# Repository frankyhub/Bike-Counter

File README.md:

<div align="center">

|[:skull:ISSUE](https://github.com/frankyhub/Bike-Counter/issues?q=is%3Aissue)|[:speech_balloon: Forum /Discussion](https://github.com/frankyhub/Bike-Counter/discussions)|[:grey_question:WiKi](https://github.com/frankyhub/Bike-Counter/wiki)||
|--|--|--|--|
| | | | |
||<a href="https://github.com/frankyhub/Bike-Counter/issues">|<a href="https://github.com/frankyhub/Bike-Counter/discussions">|<a href="https://github.com/frankyhub/Bike-Counter/releases">|
|| <a href="https://github.com/frankyhub/Bike-Counter/pulse" alt="Activity">| <a href="https://github.com/frankyhub/Bike-Counter/graphs/traffic">  |<a href="https://github.com/frankyhub?tab=stars"> |
</div>

# Bike-Counter

## Story
Der Bike-Counter zählt Bikes auf einer Nebenstraße in zwei unterschiedlichen Richtungen und sendet die Zählerstände an eine SQL-Datenbank. Es sollen nur Bikes gezählt werden und keine Fußgänger oder andere Fahrzeuge. Mit einem Dashboard werden die Zählerstände der Bikes angezeigt. Eine Auswertung zeigt die Durchfahrt der Bikes innerhalb der letzten 24 Stunden. Für die Erfassung der Bikes werden 2 Lichtschranken verwendet.

Vorteile des Bike-Counters: 
+ Verwendung von handelsüblichen Sensoren (Drucksensor, Lichtschranke ...)
+ Richtungserkennung der Fahrräder
+ Zählerstände auf einem Dashboard visualisiert
+ Auswertung der Bewegungen der letzten 24h
+ Nutzung der kostenlosen SQL-Datenbank des Providers (Strato)

## Hardware
+ 1 x ESP32
+ 2 x Lichtschranken PEM2D
+ 1 x Platine (Richtungserkennung)

## Software
+ Die Zählimpulse der Lichtschranken werden von der "Richtungserkennung-Platine" aufbereitet.
+ Der ESP32 übermittelt die Zählerstände an das PHP-Programm "post-data.php".
+ Die Zählerstände werden in einer SQL-Datenbank gespeichert und mit dem Dashboard "hoki-counter.php angezeigt.
+ Eine 24h-Auswertung kann mit dem Programm "auswertung.php" erfolgen.

---

<div style="position:absolute; left:2cm; ">   
<ol class="breadcrumb" style="border-top: 2px solid black;border-bottom:2px solid black; height: 45px; width: 900px;"> <p align="center"><a href="#oben">nach oben</a></p></ol>
</div>  

---

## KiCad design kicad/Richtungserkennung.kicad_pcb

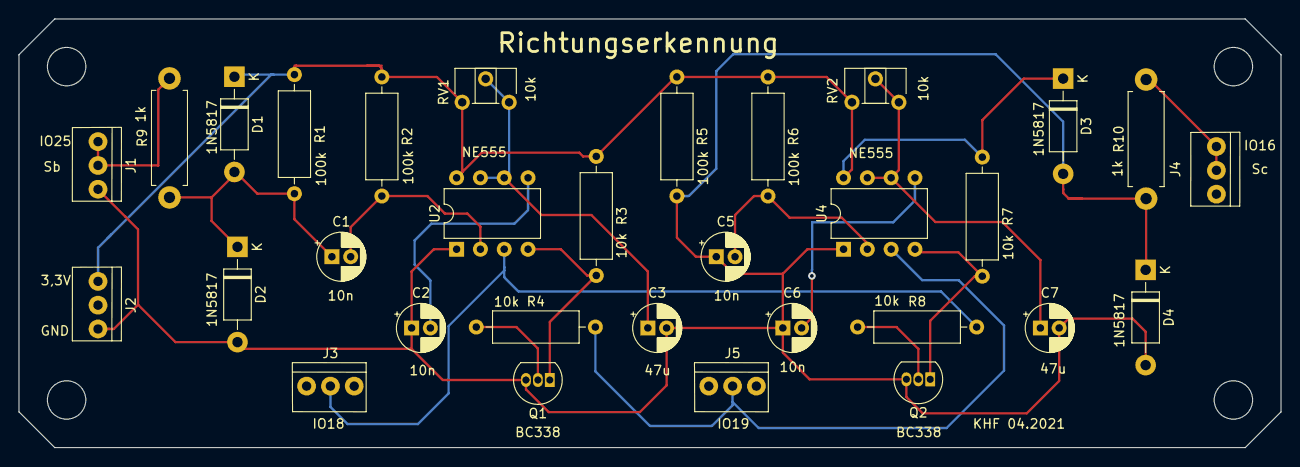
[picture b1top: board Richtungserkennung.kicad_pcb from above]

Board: 2 copper layers, 134.6 x 45.7 mm, 31 parts (0 on the bottom side), 17 nets.

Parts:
C1, C2, C5, C6: 10nF; CP_Radial_D5.0mm_P2.00mm
C3, C7: CP; CP_Radial_D5.0mm_P2.00mm
D1, D2, D3, D4: 1N5817; D_DO-41_SOD81_P10.16mm_Horizontal
J1, J2, J3, J4, J5: PL-Stecker_3pol_ohne_Beschriftung; PL-Stecker3pol
Q1, Q2: BC338; TO-92_Inline
R1, R2, R5, R6: 100k; R_Axial_DIN0309_L9.0mm_D3.2mm_P12.70mm_Horizontal
R3, R7: 10k; R_Axial_DIN0309_L9.0mm_D3.2mm_P12.70mm_Horizontal
R4, R8: R; R_Axial_DIN0309_L9.0mm_D3.2mm_P12.70mm_Horizontal
R9, R10: 1k; R_Axial_DIN0411_L9.9mm_D3.6mm_P12.70mm_Horizontal
RV1: 10k; Potentiometer_Piher_PT-6-H_Horizontal
RV2: 100k; Potentiometer_Piher_PT-6-H_Horizontal
U2, U4: NE555D; DIP-8_W7.62mm

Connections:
unnamed: C1.1, D1.2, D2.1, R1.2, R9.1
unnamed: C1.2, R2.2, U2.2
unnamed: C2.1, C3.2, C5.1, C6.1, C7.2, D2.2, D3.2, D4.1, D4.2, J1.3, J2.3, Q1.3, Q2.3, R5.2, R10.1, U2.1, U4.1
unnamed: C2.2, U2.5
unnamed: C3.1, RV1.2, RV1.3, U2.6, U2.7
unnamed: C5.2, R6.2, U4.2
unnamed: C6.2, U4.5
unnamed: C7.1, RV2.2, RV2.3, U4.6, U4.7
unnamed: D1.1, D3.1, J2.1, R1.1, R2.1, R3.1, R5.1, R6.1, R7.1, RV1.1, RV2.1, U2.8, U4.8
unnamed: J1.1, J1.2, R9.2
unnamed: J3.2, R8.2, U2.3
unnamed: J4.1, J4.2, R10.2
unnamed: J5.2, R4.2, U4.3
unnamed: Q1.1, R3.2, U2.4
unnamed: Q1.2, R4.1
unnamed: Q2.1, R7.2, U4.4
unnamed: Q2.2, R8.1

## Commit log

2024-08-16 V 28.06.2021
2024-10-12 V12102024
